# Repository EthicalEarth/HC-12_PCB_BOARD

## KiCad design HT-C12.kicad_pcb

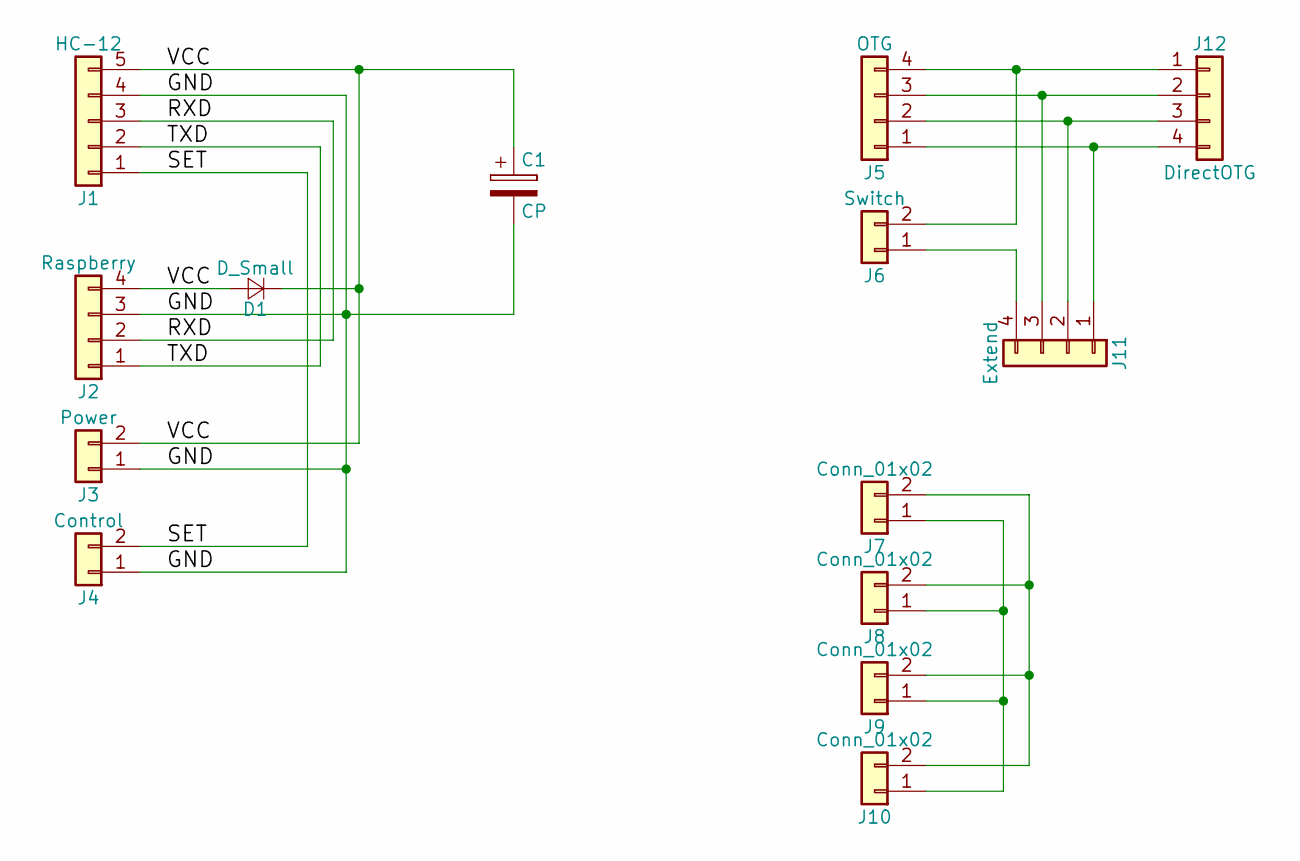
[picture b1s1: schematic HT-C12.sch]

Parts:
C1: CP; CP_Radial_D5.0mm_P2.50mm
D1: D_Small; D_SOD-123
J1: HC-12; Socket_Strip_Straight_1x05_Pitch2.54mm
J2: Raspberry; Pin_Header_Straight_1x04_Pitch2.54mm
J3: Power; Pin_Header_Straight_1x02_Pitch2.54mm
J4: Control; Socket_Strip_Straight_1x02_Pitch2.54mm
J5: OTG; Pin_Header_Straight_1x04_Pitch2.54mm
J6: Switch; Pin_Header_Straight_1x02_Pitch2.54mm
J7, J8, J9, J10: Conn_01x02; Pin_Header_Straight_1x02_Pitch2.54mm
J11: Extend; Pin_Header_Straight_1x04_Pitch2.54mm
J12: DirectOTG; Pin_Header_Straight_1x04_Pitch2.54mm

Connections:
/GND: C1.2, J1.4, J2.3, J3.1, J4.1
/RXD: J1.3, J2.2
/SET: J1.1, J4.2
/TXD: J1.2, J2.1
/VCC: C1.1, D1.1 (K), D1.2 (A), J1.5, J2.4, J3.2
unnamed: J7.1, J8.1, J9.1, J10.1
unnamed: J7.2, J8.2, J9.2, J10.2
unnamed: J5.1, J11.1, J12.4
unnamed: J5.2, J11.2, J12.3
unnamed: J5.3, J11.3, J12.2
unnamed: J6.1, J11.4
unnamed: J5.4, J6.2, J12.1

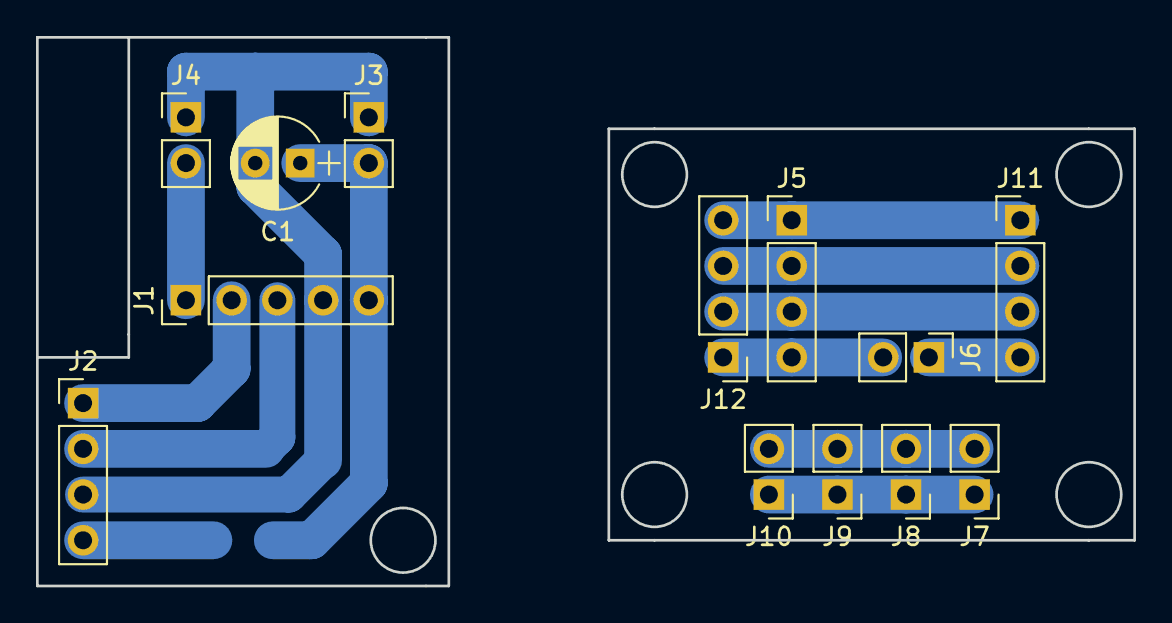
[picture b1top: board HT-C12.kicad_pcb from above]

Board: 2 copper layers, 61.0 x 30.5 mm, 14 parts (1 on the bottom side), 12 nets.

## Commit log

2018-07-28 Init
